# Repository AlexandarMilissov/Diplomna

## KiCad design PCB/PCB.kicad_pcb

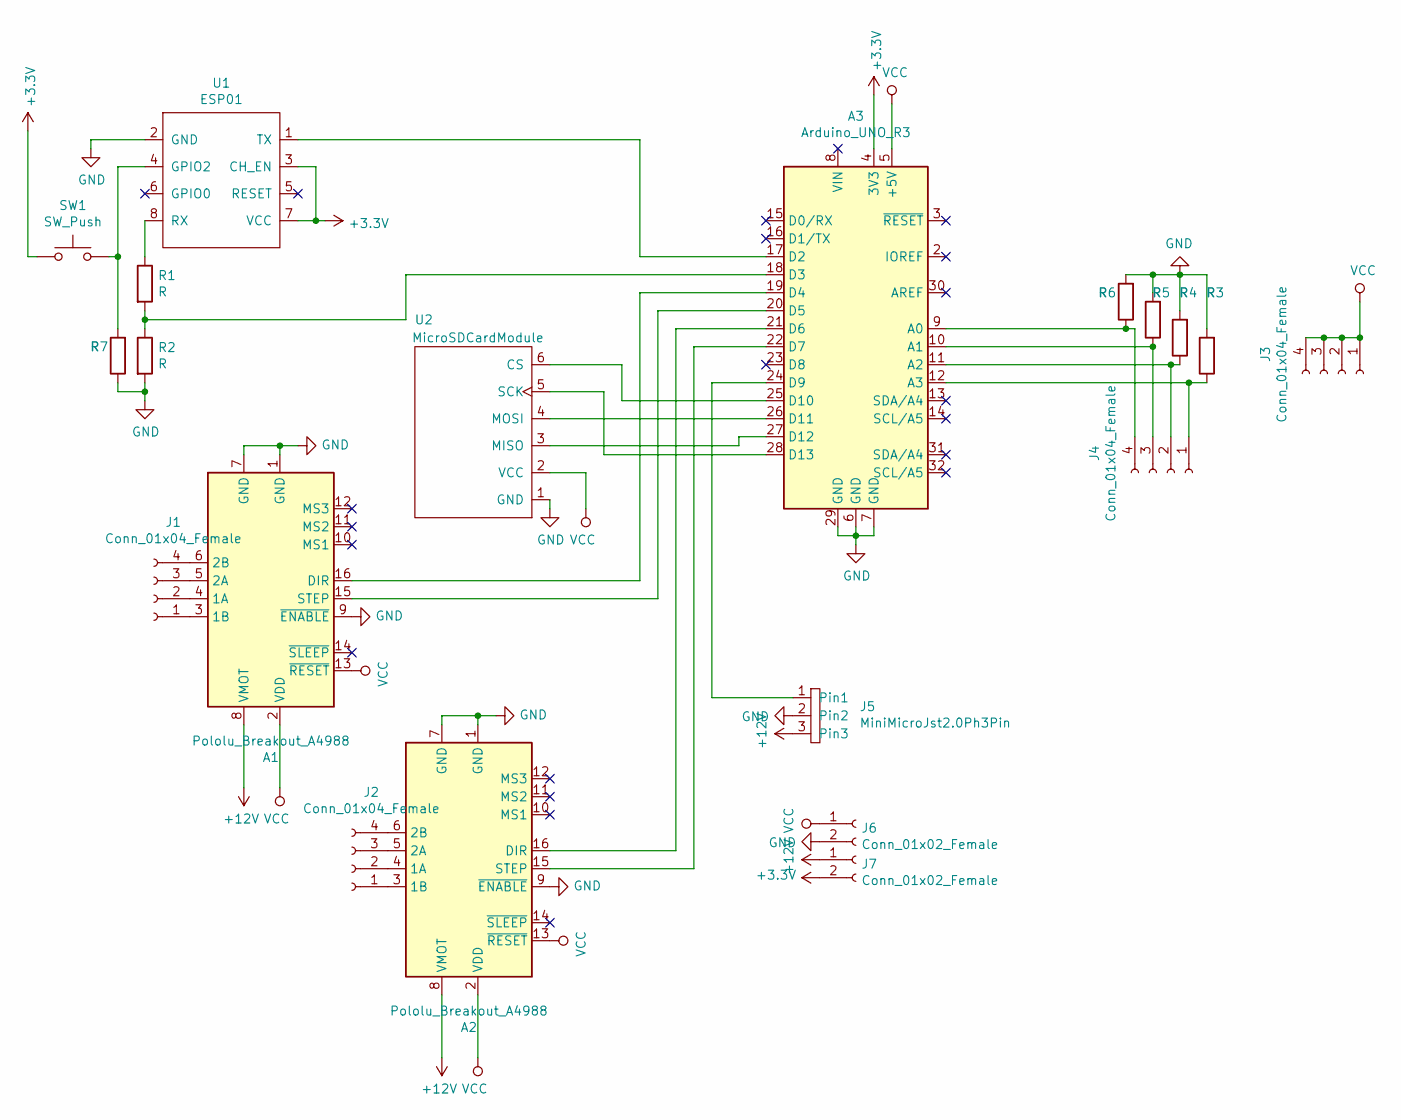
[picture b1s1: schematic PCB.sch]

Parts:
A1, A2: Pololu_Breakout_A4988; Pololu_Breakout-16_15.2x20.3mm
A3: Arduino_UNO_R3
J1, J2, J3, J4: Conn_01x04_Female; PinSocket_1x04_P2.54mm_Vertical
J5: MiniMicroJst2.0Ph3Pin; mini micro jst 2.02ph 3pin
J6, J7: Conn_01x02_Female; PinSocket_1x02_P2.54mm_Vertical
R1, R2, R3, R4, R5, R6, R7: R; R_Axial_DIN0411_L9.9mm_D3.6mm_P12.70mm_Horizontal
SW1: SW_Push; SW_PUSH_6mm
U1: ESP01; ESP-01
U2: MicroSDCardModule; PinSocket_1x06_P2.54mm_Vertical

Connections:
+3V3: A3.4 (3V3), J7.2, SW1.1, U1.3 (CH_EN), U1.7 (VCC)
+12V: A1.8 (VMOT), A2.8 (VMOT), J5.3 (Pin3), J7.1
GND: A1.1 (GND), A1.7 (GND), A1.9 (~ENABLE), A2.1 (GND), A2.7 (GND), A2.9 (~ENABLE), A3.6 (GND), A3.7 (GND), A3.29 (GND), J5.2 (Pin2), J6.2, R2.2, R3.2, R4.2, R5.2, R6.2, R7.1, U1.2 (GND), U2.1 (GND)
unnamed: A1.3 (1B), J1.1
unnamed: A1.4 (1A), J1.2
unnamed: A1.5 (2A), J1.3
unnamed: A1.6 (2B), J1.4
unnamed: A1.15 (STEP), A3.20 (D5)
unnamed: A1.16 (DIR), A3.19 (D4)
unnamed: A2.3 (1B), J2.1
unnamed: A2.4 (1A), J2.2
unnamed: A2.5 (2A), J2.3
unnamed: A2.6 (2B), J2.4
unnamed: A2.15 (STEP), A3.22 (D7)
unnamed: A2.16 (DIR), A3.21 (D6)
unnamed: A3.9 (A0), J4.4, R6.1
unnamed: A3.10 (A1), J4.3, R5.1
unnamed: A3.11 (A2), J4.2, R4.1
unnamed: A3.12 (A3), J4.1, R3.1
unnamed: A3.17 (D2), U1.1 (TX)
unnamed: A3.18 (D3), R1.2, R2.1
unnamed: A3.24 (D9), J5.1 (Pin1)
unnamed: A3.25 (D10), U2.6 (CS)
unnamed: A3.26 (D11), U2.4 (MOSI)
unnamed: A3.27 (D12), U2.3 (MISO)
unnamed: A3.28 (D13), U2.5 (SCK)
unnamed: R1.1, U1.8 (RX)
unnamed: R7.2, SW1.2, U1.4 (GPIO2)
VCC: A1.2 (VDD), A1.13 (~RESET), A2.2 (VDD), A2.13 (~RESET), A3.5 (+5V), J3.1, J3.2, J3.3, J3.4, J6.1, U2.2 (VCC)

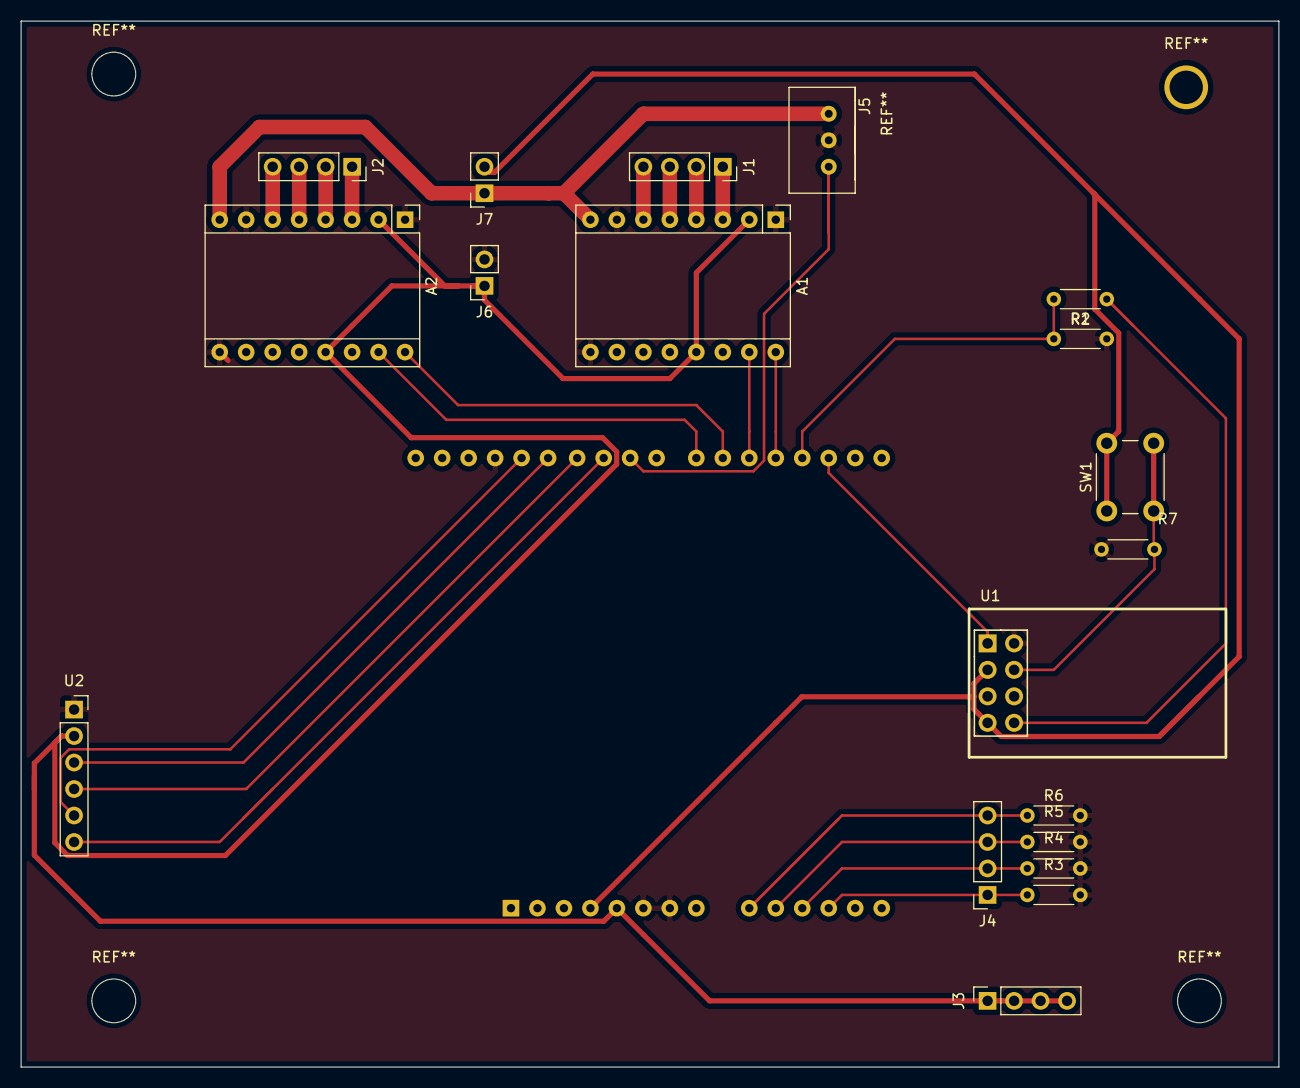
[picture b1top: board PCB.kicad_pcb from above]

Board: 2 copper layers, 120.6 x 100.3 mm, 20 parts (1 on the bottom side), 29 nets.

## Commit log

2020-01-18 App part 1 done
2020-01-18 bug fixing and simple file select
2020-01-18 bitmap convertor WIP
2020-01-20 image to bit array and send
2020-01-20 bugfixing
